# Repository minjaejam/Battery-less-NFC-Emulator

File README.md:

https://github.com/user-attachments/assets/a0f929fd-fd86-4b5f-9a33-4b0fc378b6a2

https://github.com/user-attachments/assets/47e20b58-1ad2-490b-87c6-6bac8df01a59

■ 주요 기능
1. 배터리 없이 동작
2. 13.56 MHz NFC 통신
3. MCU 기반 NFC 태그 에뮬레이션
4. ISO/IEC 14443 Type A 통신
5. PCB Loop Antenna 사용

■ 현재 지원
1. mifare classic 1k
2. ntag215 (시연을 위해 닌텐도 스위치 amiibo 데이터를 이용)

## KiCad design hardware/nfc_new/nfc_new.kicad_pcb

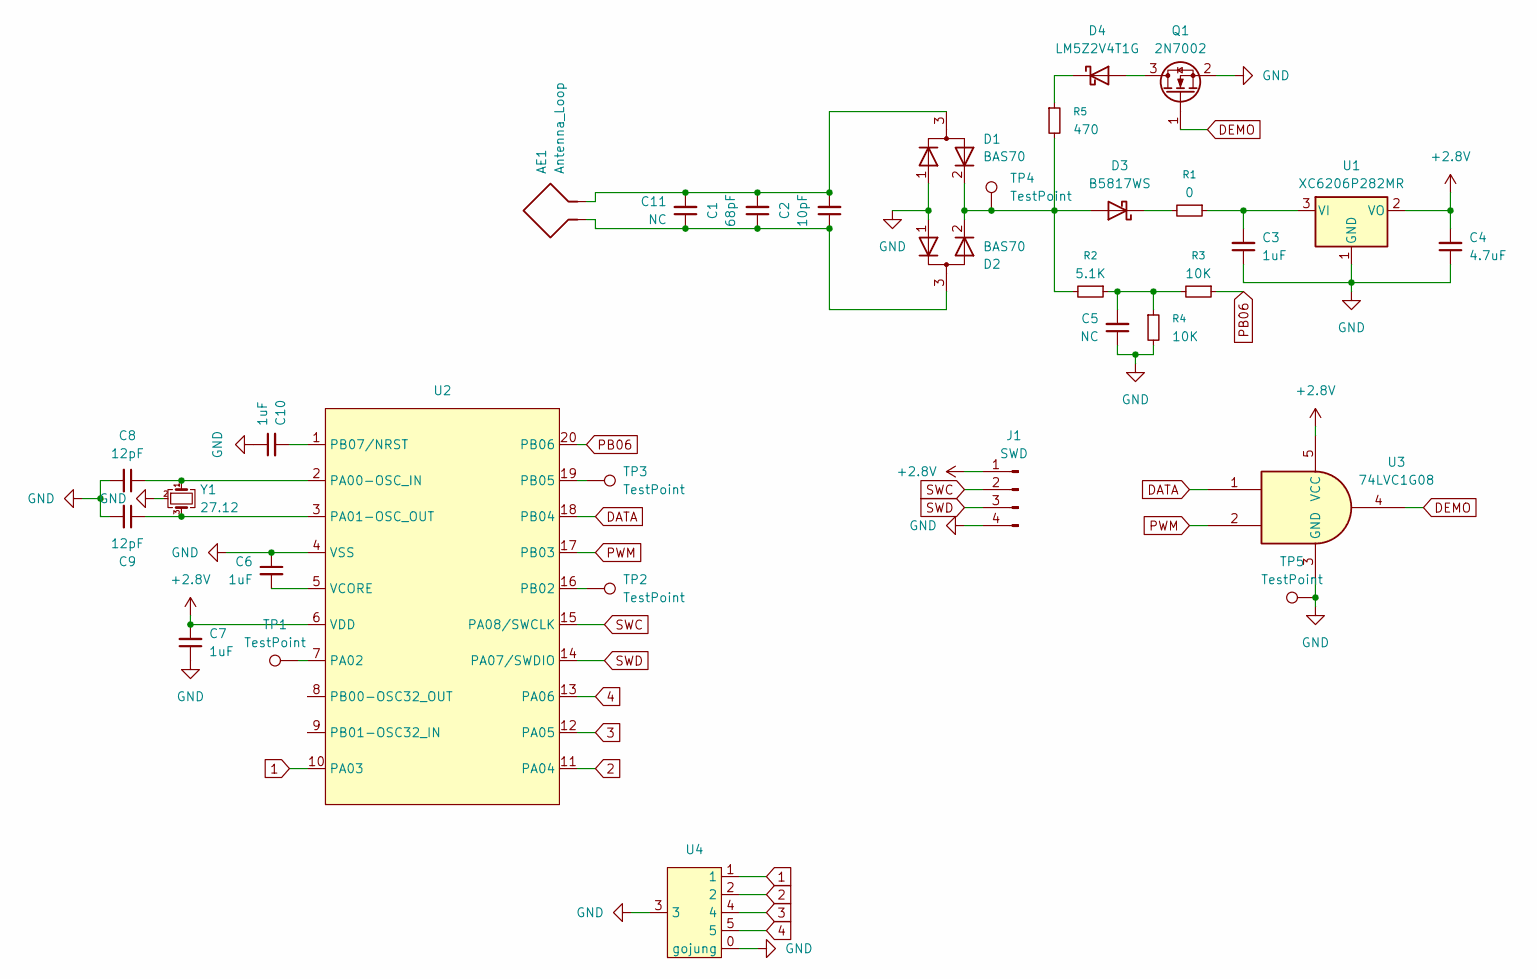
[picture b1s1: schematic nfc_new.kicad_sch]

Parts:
AE1: Antenna_Loop; 1.8uH_2
C1: 68pF; C_0805_2012Metric_Pad1.18x1.45mm_HandSolder
C2: 10pF; C_0805_2012Metric_Pad1.18x1.45mm_HandSolder
C3, C6, C7, C10: 1uF; C_0805_2012Metric_Pad1.18x1.45mm_HandSolder
C4: 4.7uF; C_0805_2012Metric_Pad1.18x1.45mm_HandSolder
C5, C11: NC; C_0805_2012Metric_Pad1.18x1.45mm_HandSolder
C8, C9: 12pF; C_0805_2012Metric_Pad1.18x1.45mm_HandSolder
D1, D2: BAS70; SOT-323_SC-70
D3: B5817WS; D_SOD-323_HandSoldering
D4: LM5Z2V4T1G; D_SOD-523
J1: SWD; PinHeader_1x04_P2.54mm_Vertical
Q1: 2N7002; SOT-23
R1: 0; R_0805_2012Metric_Pad1.20x1.40mm_HandSolder
R2: 5.1K; R_0805_2012Metric_Pad1.20x1.40mm_HandSolder
R3, R4: 10K; R_0805_2012Metric_Pad1.20x1.40mm_HandSolder
R5: 470; R_0805_2012Metric_Pad1.20x1.40mm_HandSolder
TP1, TP2, TP3, TP4, TP5: TestPoint; TestPoint_Pad_D1.0mm
U1: XC6206P282MR; SOT-23-3
U2: QFN-20-1EP_3x3mm_P0.4mm_EP1.65x1.65mm_ThermalVias
U3: 74LVC1G08; SOT-23-5_HandSoldering
U4: spd4
Y1: 27.12; Crystal_SMD_3225-4Pin_3.2x2.5mm_HandSoldering

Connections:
1: U2.10 (PA03), U4.1
2: U2.11 (PA04), U4.2
3: U2.12 (PA05), U4.4
4: U2.13 (PA06), U4.5
+2.8V: C4.2, C7.2, J1.1, U1.2 (VO), U2.6 (VDD), U3.5 (VCC)
DATA: U2.18 (PB04), U3.1
DEMO: Q1.1 (G), U3.4
GND: C3.1, C4.1, C5.1, C6.1, C7.1, C8.2, C9.2, C10.1, D1.1 (A), D2.1 (A), J1.4, Q1.2 (S), R4.2, TP5.1 (1_1), U1.1 (GND), U2.4 (VSS), U2.21 (VSS), U3.3 (GND), U4.0 (gojung), U4.3, Y1.2 (G), Y1.4 (G)
unnamed: C5.2, R2.1, R3.2, R4.1
unnamed: D1.2 (K), D2.2 (K), D3.2 (A), R2.2, R5.2, TP4.1 (1_1)
unnamed: AE1.2, C1.2, C2.2, C11.2, D1.3 (common)
unnamed: AE1.1, C1.1, C2.1, C11.1, D2.3 (common)
unnamed: D3.1 (K), R1.2
unnamed: D4.2 (A), Q1.3 (D)
unnamed: D4.1 (K), R5.1
unnamed: C3.2, R1.1, U1.3 (VI)
unnamed: C8.1, U2.2 (PA00-OSC_IN), Y1.1
unnamed: C9.1, U2.3 (PA01-OSC_OUT), Y1.3
unnamed: TP1.1 (1_1), U2.7 (PA02)
unnamed: TP2.1 (1_1), U2.16 (PB02)
unnamed: TP3.1 (1_1), U2.19 (PB05)
unnamed: C10.2, U2.1 (PB07/NRST)
unnamed: C6.2, U2.5 (VCORE)
PB06: R3.1, U2.20 (PB06)
PWM: U2.17 (PB03), U3.2
SWC: J1.2, U2.15 (PA08/SWCLK)
SWD: J1.3, U2.14 (PA07/SWDIO)

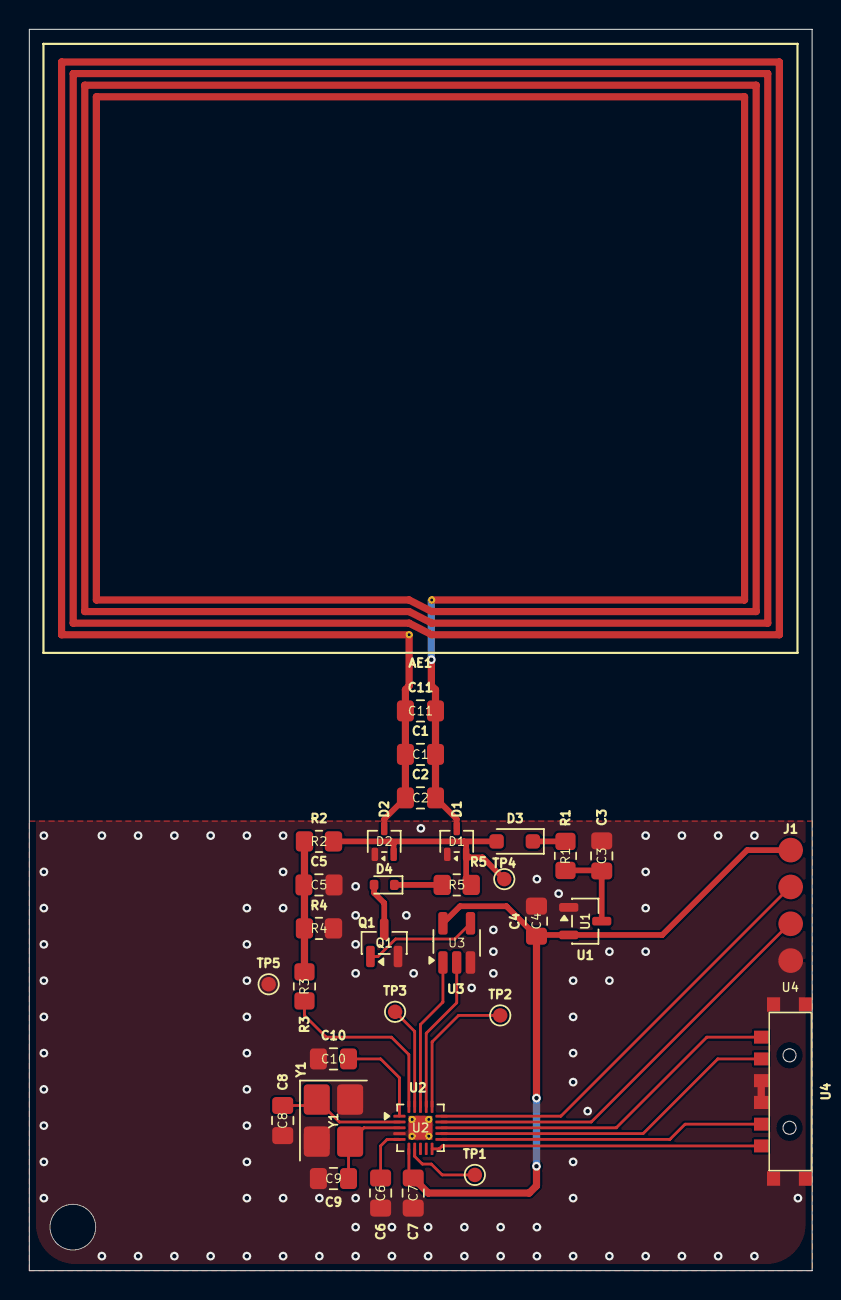
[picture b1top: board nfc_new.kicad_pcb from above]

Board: 2 copper layers, 54.0 x 85.6 mm, 33 parts (0 on the bottom side), 27 nets.
